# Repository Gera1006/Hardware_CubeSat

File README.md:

# Hardware_CubeSat
Aquí se encuentran los archivos creados para mantener un manejo más práctico de los elementos utilizados en el diseño del hardware

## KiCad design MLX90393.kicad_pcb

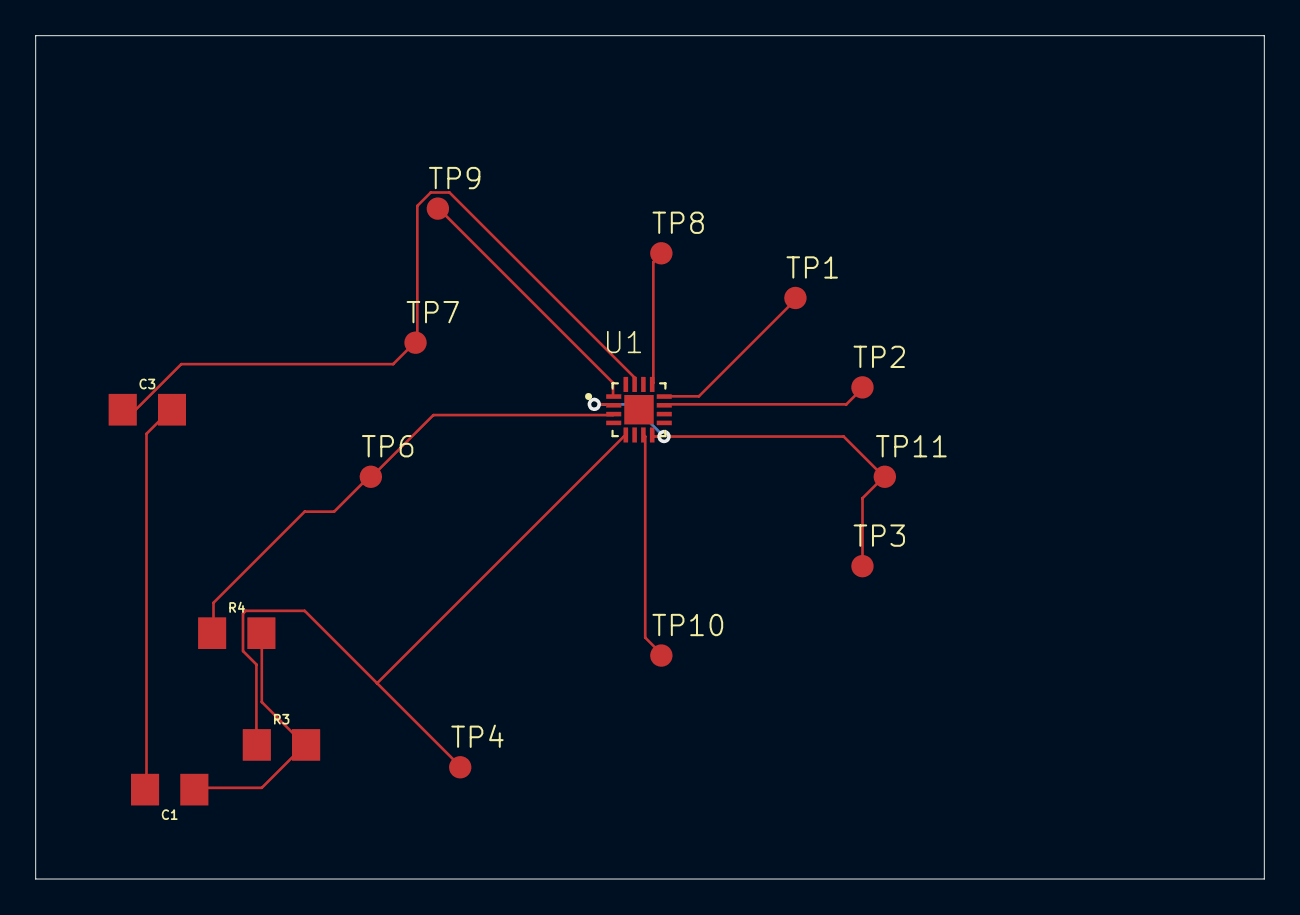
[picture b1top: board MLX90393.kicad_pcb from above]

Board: 2 copper layers, 69.8 x 47.9 mm, 15 parts (0 on the bottom side), 11 nets.

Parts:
C1, C3: 0.1u; 1206
R3, R4: 10k; 1206
TP1, TP2, TP3, TP4, TP6, TP7, TP8, TP9, TP10, TP11: TPB1,27; B1,27_385
U1: MLX90393ELW-ABA-012-SP; QFN50P300X300X100-17N

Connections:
GND: C1.2, C3.2
unnamed: TP1.TP, U1.12
unnamed: TP2.TP, U1.11
unnamed: TP9.TP, U1.1
unnamed: TP10.TP, U1.7
SCL/SCLK: R4.1, TP6.TP, U1.3
SDA/MOSI: R3.1, TP4.TP, U1.5
VDD: C3.1, TP7.TP, U1.15
VDDIO: C1.1, R3.2, R4.2
VDD_IO: TP3.TP, TP11.TP, U1.2, U1.8
VSS: TP8.TP, U1.13

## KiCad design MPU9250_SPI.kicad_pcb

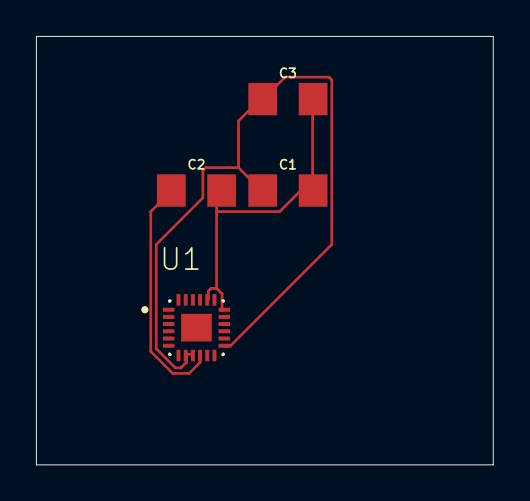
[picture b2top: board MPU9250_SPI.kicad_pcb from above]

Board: 2 copper layers, 25.4 x 23.8 mm, 4 parts (0 on the bottom side), 3 nets.

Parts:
C1, C2: 0.1uF; 1206
C3: 10nF; 1206
U1: MPU-9250; QFN40P300X300X105-25N

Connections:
GND: C1.2, C2.2, C3.2, U1.18, U1.20
unnamed: C2.1, U1.10
VDD: C1.1, C3.1, U1.8, U1.9, U1.13

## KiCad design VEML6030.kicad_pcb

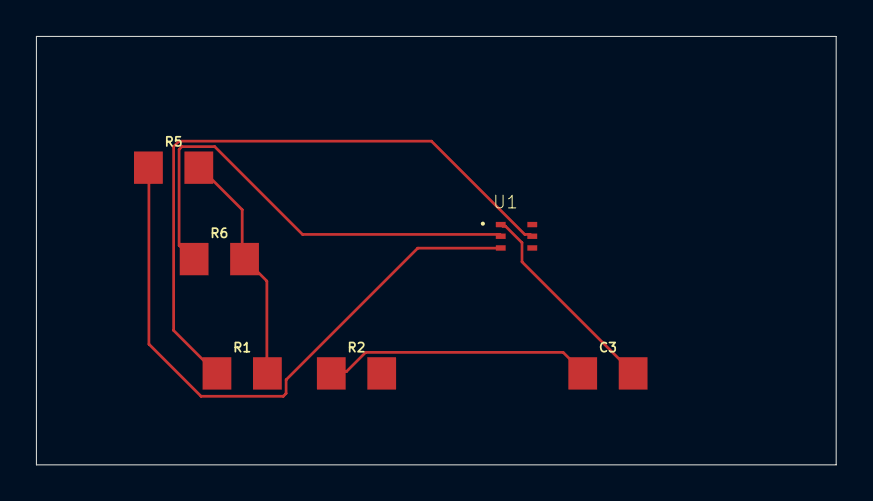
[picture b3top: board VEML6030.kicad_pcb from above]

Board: 2 copper layers, 44.4 x 23.8 mm, 6 parts (0 on the bottom side), 6 nets.

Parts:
C3: 1206
R1, R6: 2.2k; 1206
R2: 10R; 1206
R5: 10k; 1206
U1: VEML6030; VISHAY_VEML6030_2X2X0.87

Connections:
GND: C3.2, U1.1
GPIO_INTERRUPT: R5.1, U1.3
I2C_DATA_SDA: R6.1, U1.2
I2C_RELOJ_SCL: R1.1, U1.5
VCC: R1.2, R5.2, R6.2
VDD: C3.1, R2.1

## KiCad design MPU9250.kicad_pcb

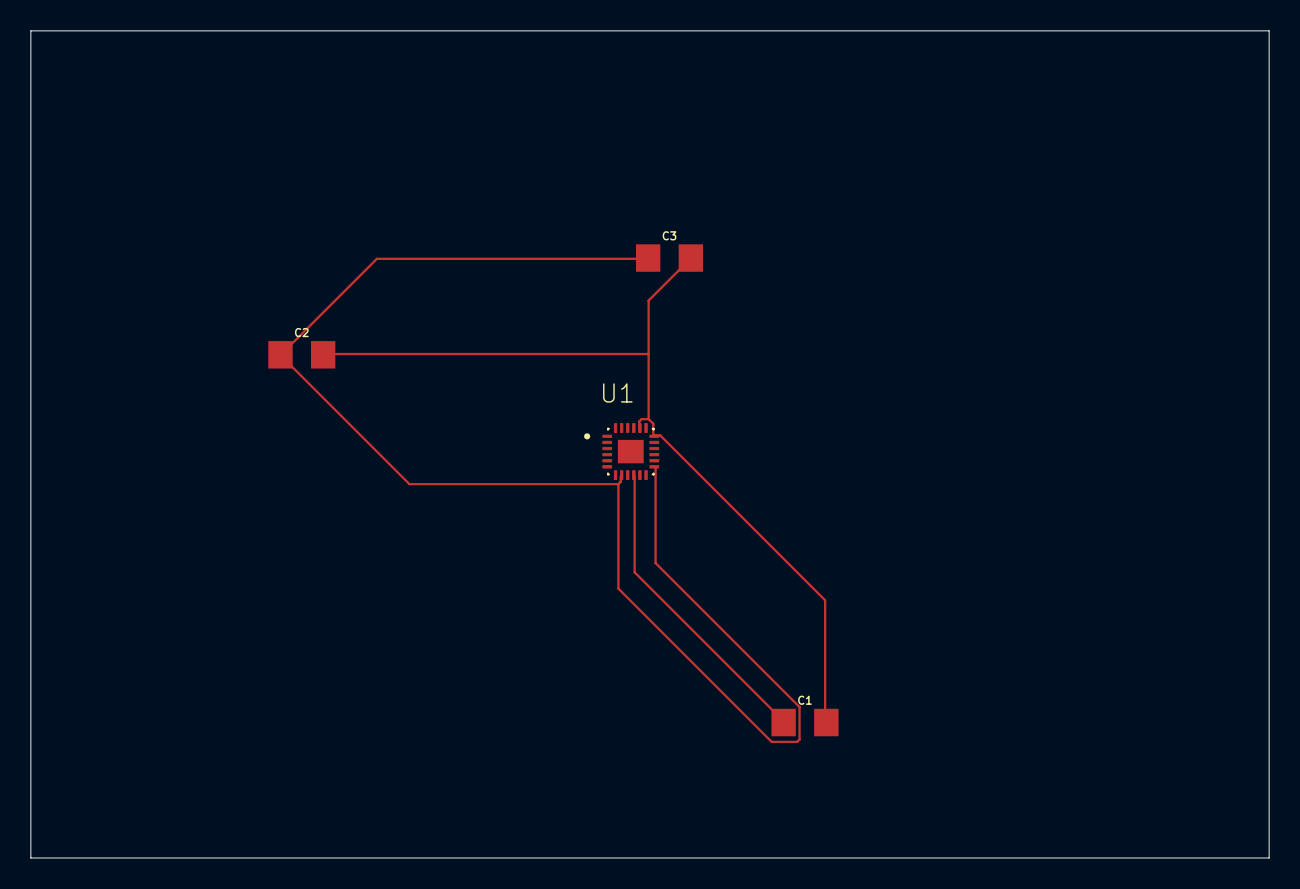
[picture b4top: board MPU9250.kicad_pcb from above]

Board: 2 copper layers, 81.3 x 54.3 mm, 4 parts (0 on the bottom side), 3 nets.

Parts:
C1, C2: 0.1uF; 1206
C3: 10nF; 1206
U1: MPU-9250; QFN40P300X300X105-25N

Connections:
GND: C1.2, C2.2, C3.2, U1.18, U1.20
unnamed: C1.1, U1.10
VDD: C2.1, C3.1, U1.8, U1.13

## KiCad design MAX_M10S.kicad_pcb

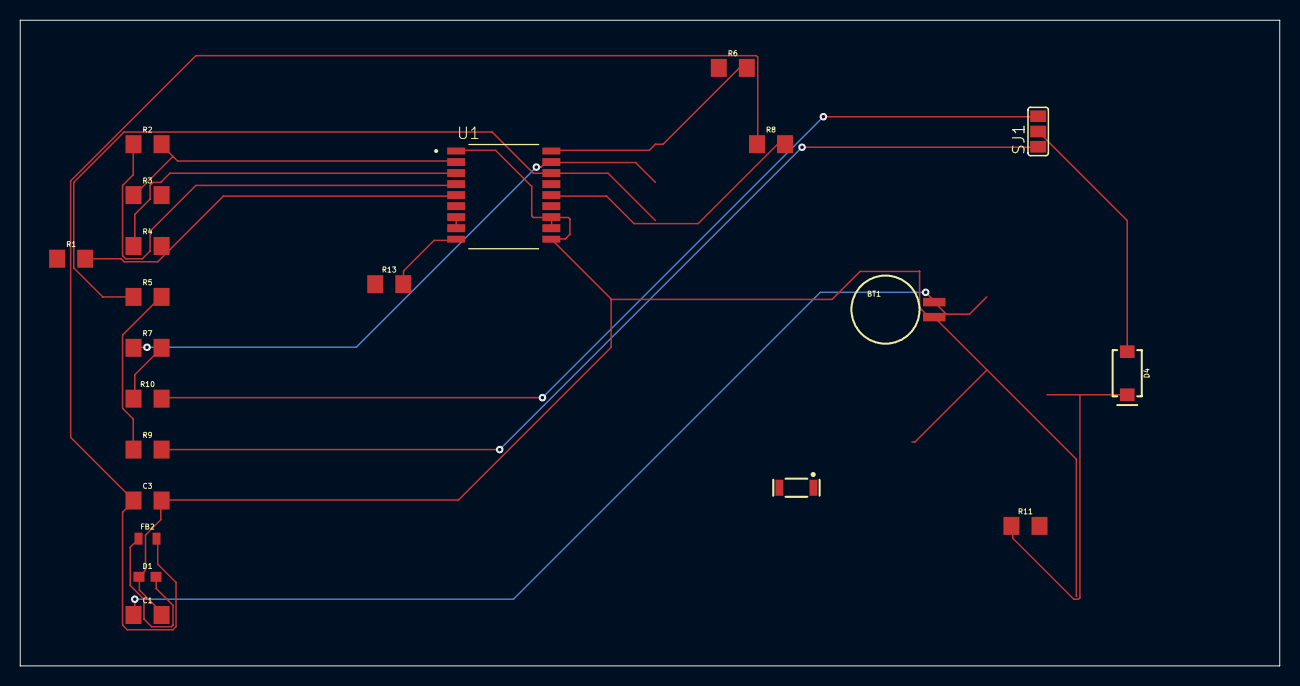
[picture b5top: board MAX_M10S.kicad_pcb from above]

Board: 2 copper layers, 125.7 x 64.4 mm, 21 parts (0 on the bottom side), 20 nets.

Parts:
A1: ANTENNA-2.4GHZ-3.2X1.6MM; ANT-2.4GHZ-3.2X1.6X1.2MM
BT1: 6.8MM_COIN_CELL; BATTCON-6.8MM
C1, C3: 1206
D1: 24V; 0603
D4: 0.5A/40V/420mV; SMA-DIODE
FB2: 600Ω; 0805
R1, R2, R3, R4, R5, R6, R7, R8, R11, R13: 33; 1206
R9, R10: 2.2k; 1206
SJ1: SJ_2_252
U1: MAX-M10S-00B; XCVR_MAX-M10S-00B

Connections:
+3V3: D4.A, SJ1.2
GND: BT1.-, C1.2, C3.2, D1.1, U1.1, U1.10, U1.12
unnamed: R2.1, U1.4
unnamed: R3.1, U1.2
unnamed: R4.1, U1.3
unnamed: R5.1, U1.16
unnamed: R7.1, U1.17
unnamed: R13.2, U1.9
unnamed: R1.2, U1.5
unnamed: R6.2, U1.18
unnamed: R10.2, SJ1.3
unnamed: R9.2, SJ1.1
unnamed: A1.FEED, D1.2, FB2.1, U1.11
unnamed: C3.1, FB2.2, R8.1
unnamed: BT1.+, C1.1
unnamed: D4.C, R11.1
SCL: R7.2, R10.1
SDA: R5.2, R9.1
SPPLY1: U1.7, U1.8
VCC_RF: R8.2, U1.14

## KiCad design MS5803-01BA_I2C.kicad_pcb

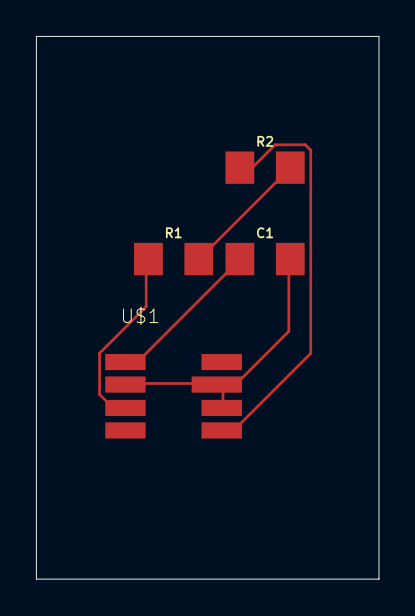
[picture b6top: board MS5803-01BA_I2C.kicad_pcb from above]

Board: 2 copper layers, 19.0 x 30.1 mm, 4 parts (0 on the bottom side), 5 nets.

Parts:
C1: 100nF; 1206
R1, R2: 1206
U$1: MS580314BA01-00; XDCR_MS580314BA01-00

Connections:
CSB: C1.2, U$1.2, U$1.3, U$1.6
PS: C1.1, U$1.5
SCLK: R2.1, U$1.1
SDA: R1.1, U$1.7
VDD: R1.2, R2.2

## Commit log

2025-01-22 Add files via upload
    Archivos design block de los sensores.
2025-01-22 Add files via upload
    Archivos sch y brd de los sensores restantes
2025-01-29 Se añaden los archivos para KiCad
    Se toman los archivos de Eagle para pasarlos al formato compatible con KiCad
